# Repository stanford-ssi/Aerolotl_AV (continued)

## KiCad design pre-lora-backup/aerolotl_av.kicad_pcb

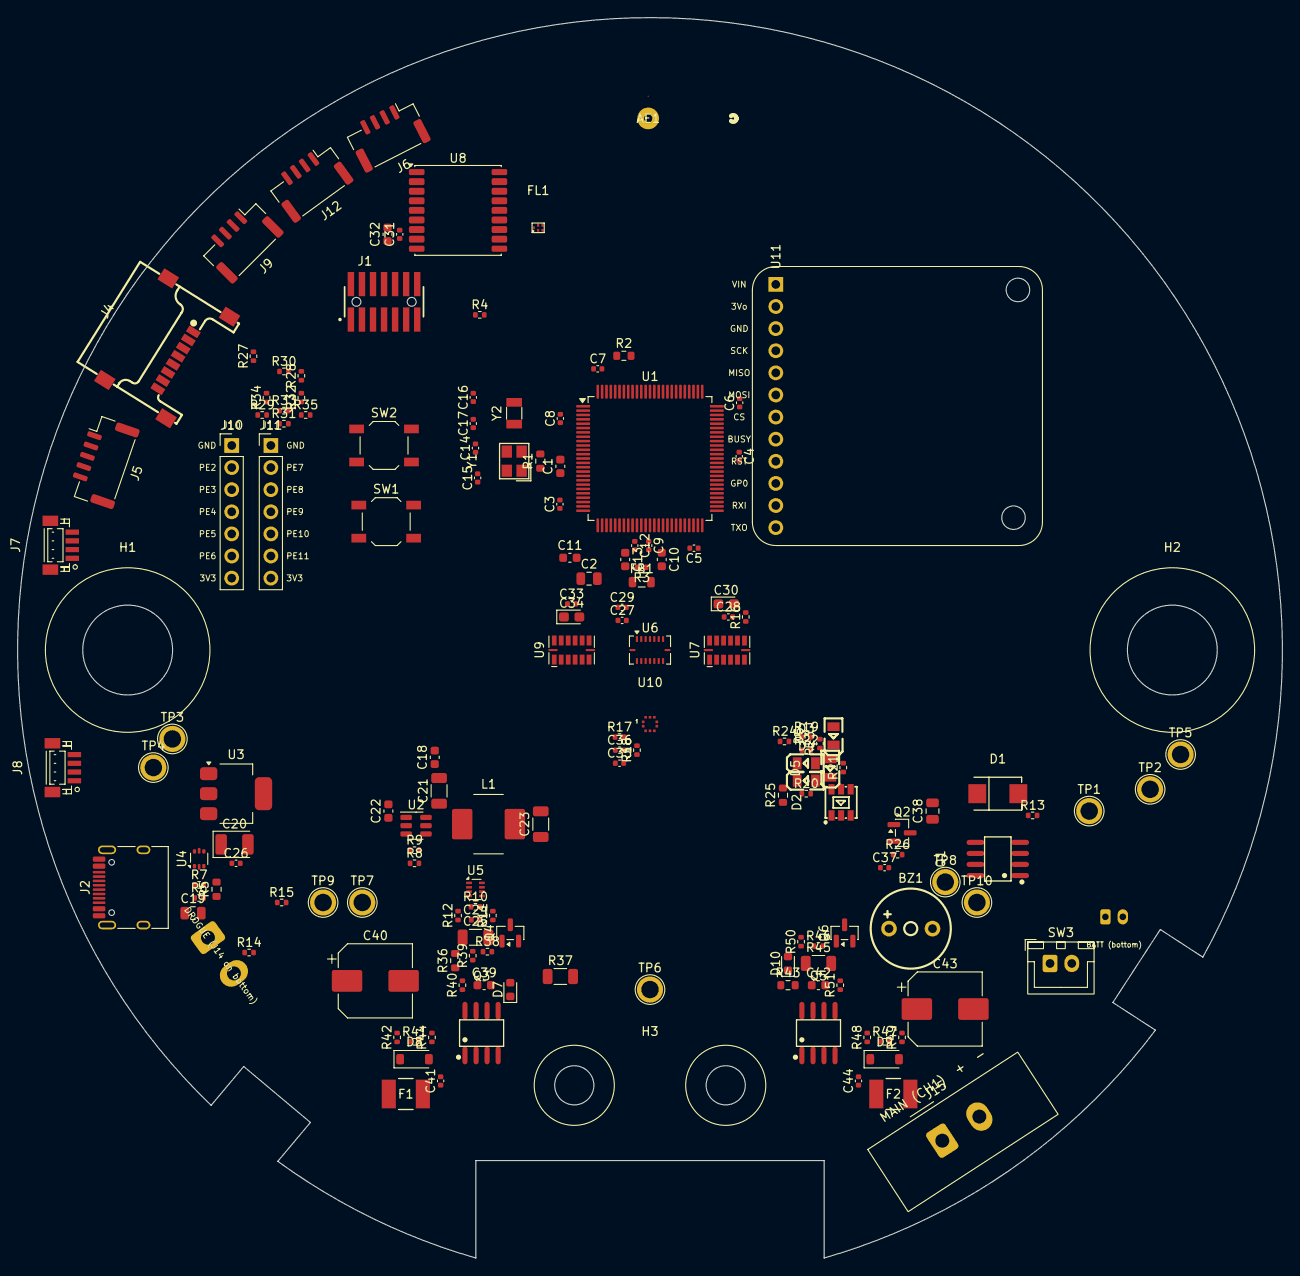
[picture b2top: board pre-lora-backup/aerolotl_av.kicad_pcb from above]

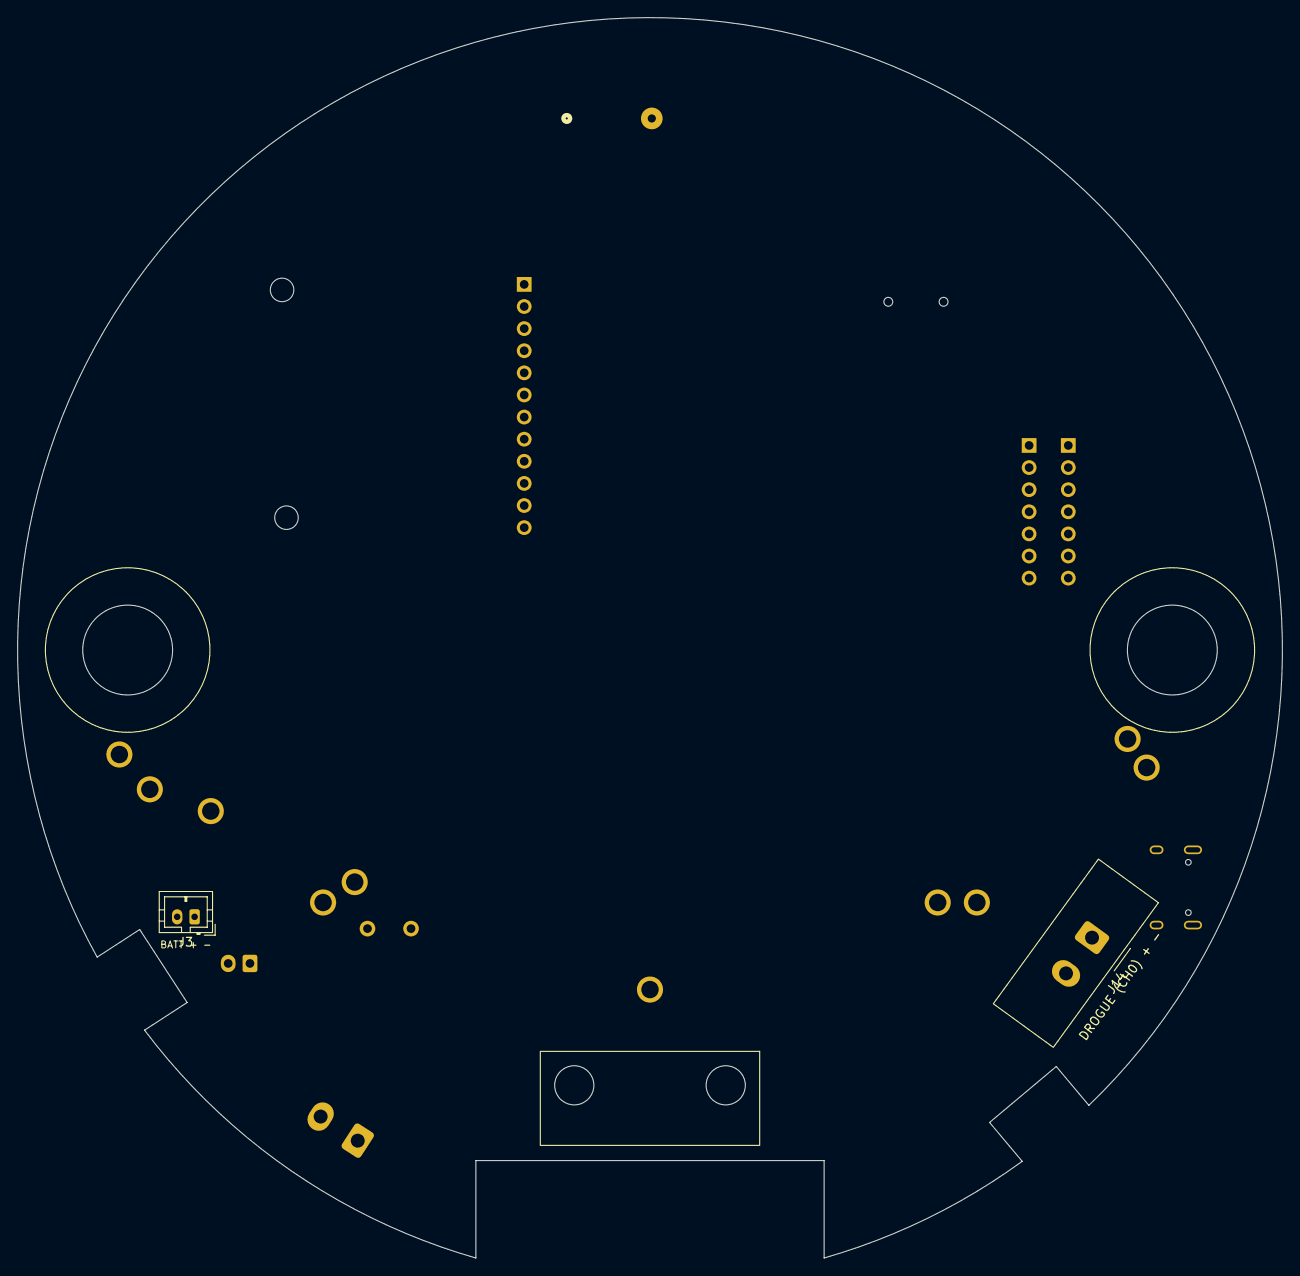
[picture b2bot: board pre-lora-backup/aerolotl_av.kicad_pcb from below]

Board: 4 copper layers, 145.3 x 142.5 mm, 161 parts (2 on the bottom side), 125 nets, no tracks yet.

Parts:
AE1: GP.1575.18.4.A.02; ANT_GP.1575.18.4.A.02_TAL
BZ1: HNB09A03; BUZ-TH_BD9.0-P5.00-D0.6-FD
C1, C18, C22: 100n; C_0603_1608Metric
C2: 4u7; C_0805_2012Metric
C3, C4, C5, C6, C7, C8, C12, C27, C28, C29, C31, C33, C35, C36, C37, C41, C44: 100n; C_0402_1005Metric
C9: 10n; C_0402_1005Metric
C10, C11, C13: 1u; C_0603_1608Metric
C14, C15: 15p; C_0402_1005Metric
C16, C17: 4.7p; C_0402_1005Metric
C19: 10u; C_0805_2012Metric
C20: 22u; CP_EIA-3528-21_Kemet-B
C21: 10u; C_1206_3216Metric
C23, C25: 100u; C_1206_3216Metric
C24, C26: 1u; C_0402_1005Metric
C30, C34: 1u; CP_EIA-2012-12_Kemet-R
C32: 10u; C_0603_1608Metric
C38: 22u; C_0805_2012Metric
C39, C42: 150n; C_0603_1608Metric
C40, C43: 330u; CP_Elec_8x10
D1: SMBJ15A; SMB_L4.6-W3.6-LS5.3-RD
D2: RS-3535MWAR-2JYJY-J; LED-SMD_RS-3535MWAR-2JYJY-J
D3: STM LED; LED0805-R-RD
D4: 3V3 LED; LED0805-R-RD
D5: USB LED; LED0805-R-RD
D6: ARM LED; LED0805-R-RD
D7, D10: LED red; LED_0603_1608Metric
D8, D9: 1N4148W; D_SOD-123
F1, F2: 1812L150/24MR; FUSE_1812L150&slash_24_LTF
FB1: 100; L_0805_2012Metric
FL1: B39162B4300F210; FILTER-SMD_5P-L1.4-W1.1_RSFPXXXXD
H1, H2: MountingHole; MountingHole_ThreadedRod_3-8in_D10.32mm
H3: TeleMetrum sled; TeleMetrum_Sled_Mount_2xM4
J1: FTSH-107-STDC14; STDC14_SAMTEC_FTSH-107-01-L-DV-K-A
J2: USB_C_Receptacle_USB2.0_16P; USB_C_Receptacle_HRO_TYPE-C-31-M-12
J3: Battery (ext.); JST_PH_B2B-PH-K_1x02_P2.00mm_Vertical
J4: TF-102-15_SD_read; TF-SMD_TF-102-15
J5: Conn_01x05_Pin; JST_GH_BM05B-GHS-TBT_1x05-1MP_P1.25mm_Vertical
J6: USART3; JST_GH_BM04B-GHS-TBT_1x04-1MP_P1.25mm_Vertical
J7, J8: StemmaQT
J9: Conn_01x04_Pin; JST_GH_BM04B-GHS-TBT_1x04-1MP_P1.25mm_Vertical
J10: GPIO_PE2-PE6; PinHeader_1x07_P2.54mm_Vertical
J11: GPIO_PE7-PE11; PinHeader_1x07_P2.54mm_Vertical
J12: LPUART1; JST_GH_BM04B-GHS-TBT_1x04-1MP_P1.25mm_Vertical
J14, J15: Screw_Terminal_01x02; TerminalBlock_Kangnex_WJ2EDGVM-5.08-02P_1x02_P5.08mm_Vertic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
L1: 5.6u; L_Cjiang_FXL0630_7.0x6.6mm
Q1: AO4407A; SOIC-8_L4.9-W3.9-P1.27-LS6.0-BL
Q2, Q4, Q6: AO3400A; SOT-23
Q3, Q5: FDS6673BZ_C467780; SOIC-8_L4.9-W3.9-P1.27-LS6.0-BL
R1, R2: 10k; R_0603_1608Metric
R3: 47; R_0402_1005Metric
R4, R38, R46: 100; R_0402_1005Metric
R5: 0R; R_0603_1608Metric
R6, R7: 5k1; R_0402_1005Metric
R8, R13: 100k; R_0402_1005Metric
R9: 22k1; R_0402_1005Metric
R10: 9k53; R_0402_1005Metric
R11, R14, R27, R28, R29, R30, R31, R41, R44, R47, R49: 10k; R_0402_1005Metric
R12: 4k99; R_0402_1005Metric
R15, R26: 3k3; R_0402_1005Metric
R16, R17, R18, R32, R33, R34, R35: 10; R_0402_1005Metric
R19, R20, R21, R40, R51: 330; R_0402_1005Metric
R22, R23: 470; R_0402_1005Metric
R24: 910; R_0402_1005Metric
R25, R36, R43: 3k3; R_0603_1608Metric
R37, R45: 1k; R_1206_3216Metric
R39, R50: 8k2; R_0402_1005Metric
R42, R48: 33k; R_0402_1005Metric
SW1: SW_SPST; SW_SPST_TL3342
SW2: SW_Push; SW_SPST_TL3342
SW3: SW_SPST; JST_XH_B2B-XH-A_1x02_P2.50mm_Vertical
TP1: +BATT; TestPoint_Plated_Hole_D2.0mm
TP2: +12V; TestPoint_Plated_Hole_D2.0mm
TP3: +3V3; TestPoint_Plated_Hole_D2.0mm
TP4: VOLT_SENSE; TestPoint_Plated_Hole_D2.0mm
TP5: GND; TestPoint_Plated_Hole_D2.0mm
TP6: +12V_ARM; TestPoint_Plated_Hole_D2.0mm
TP7: SENSE_I0; TestPoint_Plated_Hole_D2.0mm
TP8: SENSE_I1; TestPoint_Plated_Hole_D2.0mm
TP9: IGNITE_0; TestPoint_Plated_Hole_D2.0mm
TP10: IGNITE_1; TestPoint_Plated_Hole_D2.0mm
U1: STM32G474VETx; LQFP-100_14x14mm_P0.5mm
U2: LMR51430XFDDCR; TSOT-23-6
U3: AMS1117-3.3; SOT-223-3_TabPin2
U4: USBLC6-2P6; SOT-666
U5: TPS2116DRL; SOT-583-8
U6: BMI088; Bosch_LGA-16_4.5x3mm_P0.5mm_LayoutBorder7x1y_ClockwisePinNu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
U7: ADXL345BCCZ-RL7; ADI_LGA-14_3x5mm_P0.8mm
U8: MAX-M10S; ublox_MAX
U9: ADXL375BCCZ-RL7; ADI_LGA-14_3x5mm_P0.8mm
U10: BMP581; LGA-10_L2.0-W2.0-P0.50-TL_BMP581
U11: Airlift; Ada_Airlift
Y1: 25MHz; CRYSTAL-SMD_4P-L3.2-W2.5-BL
Y2: 32.768kHz; Crystal_SMD_3215-2Pin_3.2x1.5mm

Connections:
+3.3VA: C9.1, C10.1, FB1.1, R3.1, U1.37 (VDDA)
+3V3: BZ1.1 (+), C2.1, C3.1, C4.1, C5.1, C6.1, C7.1, C8.1, C11.1, C25.1, C27.1, C28.1, C29.1, C31.1, C32.1, C33.1, C34.1, C37.1, C38.1, D2.4 (A), D2.5 (A), D2.6 (A), D4.1 (+), D8.2 (A), D9.2 (A), FB1.2, J1.03, J4.4 (VDD), J5.5, J6.4, J7.2, J8.2, J9.4, J10.7, J11.7, J12.4, R1.1, R11.1, R16.1, R17.1, R18.1, R27.1, R28.1, R29.1, R30.1, R31.1, SW1.2 (B), TP3.1 (1_1), U1.6 (VBAT), U1.24 (VDD), U1.49 (VDD), U1.64 (VDD), U1.75 (VDD), U1.100 (VDD), U5.2 (VOUT), U5.7 (VOUT), U6.3 (VDD), U6.11 (VDDIO), U7.1 (VDD_I/O), U7.3 (RESERVED_3), U8.6 (V_BCKP), U8.7 (VCC_IO), U8.8 (VCC), U9.1 (VDDI/O), U9.3 (RESERVED), U9.6 (VS), U11.1 (VIN)
+3V3_BAT: C23.1, C24.1, L1.2, R8.1, R10.1, U5.3 (VIN1), U5.5 (MODE)
+5V: D5.1 (+), R5.1
+12V: C21.1, C22.1, D1.1, Q1.1 (S), Q1.2 (S), Q1.3 (S), R14.1, SW3.1 (A), TP2.1 (1_1), U2.3 (VIN), U2.5 (EN)
+12V_ARM: C39.1, C40.1, C42.1, C43.1, D6.1 (+), Q3.1 (S), Q3.2 (S), Q3.3 (S), Q5.1 (S), Q5.2 (S), Q5.3 (S), R36.2, R37.1, R43.2, R45.1, SW3.2 (B), TP6.1 (1_1)
+BATT: J3.1, Q1.5 (D), Q1.6 (D), Q1.7 (D), Q1.8 (D), TP1.1 (1_1)
/Debugger/GNDDetect: J1.11, R4.2
/Debugger/T_NRST: C1.1, J1.12, R1.2, SW2.2, U1.14 (PG10/NRST)
/Debugger/T_SWCLK: J1.06, U1.77 (PA14)
/Debugger/T_SWDIO: J1.04, U1.76 (PA13)
/Debugger/T_SWO: J1.08, U1.90 (PB3)
/Debugger/T_VCP_RX: J1.14, U1.70 (PA9)
/Debugger/T_VCP_TX: J1.13, U1.71 (PA10)
/External/GPIO.PE2: J10.2, U1.1 (PE2)
/External/GPIO.PE3: J10.3, U1.2 (PE3)
/External/GPIO.PE4: J10.4, U1.3 (PE4)
/External/GPIO.PE5: J10.5, U1.4 (PE5)
/External/GPIO.PE6: J10.6, U1.5 (PE6)
/External/GPIO.PE7: J11.2, U1.38 (PE7)
/External/GPIO.PE8: J11.3, U1.39 (PE8)
/External/GPIO.PE9: J11.4, U1.40 (PE9)
/External/GPIO.PE10: J11.5, U1.41 (PE10)
/External/GPIO.PE11: J11.6, U1.42 (PE11)
/External/I2C1.SCL: J7.4, U1.78 (PA15)
/External/I2C1.SDA: J7.3, U1.94 (PB7)
/External/I2C3.SCL: J8.4, U1.67 (PC8)
/External/I2C3.SDA: J8.3, U1.68 (PC9)
/External/I2C4.SCL: J9.2, U1.65 (PC6)
/External/I2C4.SDA: J9.3, U1.66 (PC7)
/External/LPUART1_TARGET_RX: J12.2, U1.47 (PB10)
/External/LPUART1_TARGET_TX: J12.3, U1.50 (PB11)
/External/SPI4.MISO: J5.3, U1.44 (PE13)
/External/SPI4.MOSI: J5.2, U1.45 (PE14)
/External/SPI4.SCK: J5.4, U1.43 (PE12)
/External/USART3_TARGET_RX: J6.2, U1.56 (PD9)
/External/USART3_TARGET_TX: J6.3, U1.55 (PD8)
/Igniter/IGN0: D7.2 (A), Q4.1 (G), R39.1, TP9.1 (1_1), U1.61 (PD14)
/Igniter/IGN0_CONT: J14.1, Q3.5 (D), Q3.6 (D), Q3.7 (D), Q3.8 (D), R41.2, R42.1
/Igniter/IGN0_DRV: Q4.3 (D), R38.2
/Igniter/IGN0_HS_GATE: C39.2, Q3.4 (G), R37.2, R38.1
/Igniter/IGN0_LED_K: D7.1 (K), R40.1
/Igniter/IGN0_RTN: F1.2, J14.2
/Igniter/IGN1: D10.2 (A), Q6.1 (G), R50.1, TP10.1 (1_1), U1.62 (PD15)
/Igniter/IGN1_CONT: J15.1, Q5.5 (D), Q5.6 (D), Q5.7 (D), Q5.8 (D), R47.2, R48.1
/Igniter/IGN1_DRV: Q6.3 (D), R46.2
/Igniter/IGN1_HS_GATE: C42.2, Q5.4 (G), R45.2, R46.1
/Igniter/IGN1_LED_K: D10.1 (K), R51.1
/Igniter/IGN1_RTN: F2.2, J15.2
/Igniter/SENSE_I0: C41.1, R42.2, R44.1, TP7.1 (1_1), U1.20 (PA0)
/Igniter/SENSE_I1: C44.1, R48.2, R49.1, TP8.1 (1_1), U1.21 (PA1)
/Indicators/BUZZER: Q2.1 (G), R26.1, U1.69 (PA8)
/Indicators/BUZZER_DRV: BZ1.2 (-), Q2.3 (D)
/Indicators/LED: D3.1 (+), U1.60 (PD13)
/Indicators/LED.B: R21.2, U1.59 (PD12)
/Indicators/LED.G: R20.2, U1.31 (PC5)
/Indicators/LED.R: R19.2, U1.30 (PC4)
/Indicators/LED_3V3_K: D4.2 (-), R23.1
/Indicators/LED_ARM_K: D6.2 (-), R25.1
/Indicators/LED_STM_K: D3.2 (-), R22.1
/Indicators/LED_USB_K: D5.2 (-), R24.1
/Indicators/RGB_B_K: D2.1 (K), R21.1
/Indicators/RGB_G_K: D2.2 (K), R20.1
/Indicators/RGB_R_K: D2.3 (K), R19.1
/MCU/BOOT0: R2.1, SW1.1 (A), U1.95 (PB8/BOOT0)
/MCU/GPS_RST: U1.91 (PB4), U8.9 (~RESET)
/MCU/HS_OSC_A: C14.1, U1.12 (PF0), Y1.1 (OSC1)
/MCU/HS_OSC_B: C15.1, U1.13 (PF1), Y1.3 (OSC2)
/MCU/LS_OSC_A: C17.1, U1.8 (PC14), Y2.2
/MCU/LS_OSC_B: C16.1, U1.9 (PC15), Y2.1
/MCU/PWR_STS: R11.2, U1.16 (PC1), U5.8 (ST)
/MCU/SDSPI.CS: R33.1, U1.82 (PD0)
/MCU/SDSPI.MISO: R35.1, U1.80 (PC11)
/MCU/SDSPI.MOSI: R32.1, U1.81 (PC12)
/MCU/SDSPI.SCK: R34.1, U1.79 (PC10)
/MCU/SPI1.CS_345: U1.88 (PD6), U7.7 (~CS)
/MCU/SPI1.CS_375: U1.89 (PD7), U9.7 (~CS)
/MCU/SPI1.CS_BMP: U1.87 (PD5), U10.6 (CSB)
/MCU/SPI1.CS_IMU_ACC: U1.85 (PD3), U6.14 (~CSB1)
/MCU/SPI1.CS_IMU_GYRO: U1.86 (PD4), U6.5 (~CSB2)
/MCU/SPI1.INT_345: U1.32 (PB0), U7.8 (INT1)
/MCU/SPI1.INT_375: U1.96 (PB9), U9.8 (INT1)
/MCU/SPI1.INT_BMP: U1.33 (PB1), U10.7 (INT)
/MCU/SPI1.INT_IMU_ACC: U1.46 (PE15), U6.16 (INT1)
/MCU/SPI1.INT_IMU_GYRO: U1.34 (PB2), U6.12 (INT3)
/MCU/SPI1.MISO: U1.28 (PA6), U6.10 (SDO2), U6.15 (SDO1), U7.12 (SDO/ALT_ADDRESS), U9.12 (SDO/ALTADDRESS), U10.5 (SDO)
/MCU/SPI1.MOSI: U1.29 (PA7), U6.9 (SDI/SDA), U7.13 (SDA/SDI/SDIO), U9.13 (SDA/SDI/SDIO), U10.4 (SDI)
/MCU/SPI1.SCK: U1.27 (PA5), U6.8 (SCK/SCL), U7.14 (SCL/SCLK), U9.14 (SCL/SCLK), U10.2 (SCK)
/MCU/SPI2.BUSY: U1.57 (PD10), U11.8 (BUSY)
/MCU/SPI2.CS: U1.51 (PB12), U11.7 (CS)
/MCU/SPI2.MISO: U1.53 (PB14), U11.5 (MISO)
/MCU/SPI2.MOSI: U1.54 (PB15), U11.6 (MOSI)
/MCU/SPI2.RST: U1.58 (PD11), U11.9 (~RST)
/MCU/SPI2.SCK: U1.52 (PB13), U11.4 (SCK)
/MCU/USB_D+: U1.73 (PA12), U4.4 (I/O2)
/MCU/USB_D-: U1.72 (PA11), U4.6 (I/O1)
/MCU/VREFP: C12.1, C13.1, R3.2, U1.36 (VREF+)
/Power/BUCK_CB: C18.1, U2.6 (CB)
/Power/BUCK_FB: R8.2, R9.1, U2.4 (FB)
/Power/BUCK_SW: C18.2, L1.1, U2.2 (SW)
/Power/PMUX_PR1: R10.2, R12.1, U5.4 (PR1)
/Power/P_VBUS: C19.1, J2.A4 (VBUS), J2.A9 (VBUS), J2.B4 (VBUS), J2.B9 (VBUS), R5.2, U3.3 (VI), U4.5 (VBUS)
/Power/RPP_GATE: Q1.4 (G), R13.1
/Power/USB_3V3: C20.1, C26.1, U3.2 (VO), U5.6 (VIN2)
/Power/USB_CC1: J2.A5 (CC1), R6.1
/Power/USB_CC2: J2.B5 (CC2), R7.1
/Power/USB_DM: J2.A7 (D-), J2.B7 (D-), U4.1 (I/O1)
/Power/USB_DP: J2.A6 (D+), J2.B6 (D+), U4.3 (I/O2)
/Power/VOLT_SENSE: R14.2, R15.1, TP4.1 (1_1), U1.15 (PC0)
/SD/CARD_CS: J4.2 (CD/DAT3), R30.2, R33.2
/SD/CARD_DAT1: J4.8 (DAT1), R27.2
/SD/CARD_DAT2: J4.1 (DAT2), R31.2
/SD/CARD_MISO: J4.7 (DAT0), R28.2, R35.2
/SD/CARD_MOSI: J4.3 (CMD), R29.2, R32.2
/SD/CARD_SCK: J4.5 (CLK), R34.2
/Sensors/ADXL345_VS: C30.1, R16.2, U7.6 (VS)
/Sensors/BMP581_VDD: C35.1, R18.2, U10.10 (VDD)
/Sensors/BMP581_VDDIO: C36.1, R17.2, U10.1 (VDDIO)
/Sensors/GPS_RF_ANT: AE1.1 (1_1), FL1.1 (IN)
/Sensors/GPS_RF_IN: FL1.4 (OUT), U8.11 (RF_IN)
/Sensors/M10S.RX: U1.22 (PA2), U8.3 (RXD)
/Sensors/M10S.TX: U1.25 (PA3), U8.2 (TXD)
GND: C1.2, C2.2, C3.2, C4.2, C5.2, C6.2, C7.2, C8.2, C9.2, C10.2, C11.2, C12.2, C13.2, C14.2, C15.2, C16.2, C17.2, C19.2, C20.2, C21.2, C22.2, C23.2, C24.2, C25.2, C26.2, C27.2, C28.2, C29.2, C30.2, C31.2, C32.2, C33.2, C34.2, C35.2, C36.2, C37.2, C38.2, C40.2, C41.2, C43.2, C44.2, D1.2, F1.1, F2.1, FL1.2 (GND), FL1.3 (GND), FL1.5 (GND), J1.05, J1.07, J2.A1 (GND), J2.A12 (GND), J2.B1 (GND), J2.B12 (GND), J2.SH (SHIELD), J3.2, J4.6 (VSS), J4.9 (SHELL), J4.10 (SHELL), J4.11 (SHELL), J4.12 (SHELL), J5.1, J6.1, J7.0, J7.1, J8.0, J8.1, J9.1, J10.1, J11.1, J12.1, Q2.2 (S), Q4.2 (S), Q6.2 (S), R2.2, R4.1, R6.2, R7.2, R9.2, R12.2, R13.2, R15.2, R22.2, R23.2, R24.2, R25.2, R26.2, R36.1, R39.2, R40.2, R43.1, R44.2, R49.2, R50.2, R51.2, SW2.1, TP5.1 (1_1), U1.23 (VSS), U1.35 (VSSA), U1.48 (VSS), U1.63 (VSS), U1.74 (VSS), U1.99 (VSS), U2.1 (GND), U3.1 (GND), U4.2 (GND), U5.1 (GND), U6.2 (GNDA), U6.4 (GNDA), U6.6 (GNDIO), U6.7 (PS), U7.2 (GND), U7.4 (GND), U7.5 (GND), U7.11 (RESERVED_11), U8.1 (GND), U8.10 (GND), U8.12 (GND), U9.2 (GND), U9.4 (GND), U9.5 (GND), U9.11 (RESERVED), U10.3 (VSS), U10.8 (VSS), U10.9 (VSS), U11.3 (GND), Y1.2 (GND), Y1.4 (GND)
unnamed: D8.1 (K), R41.1
unnamed: D9.1 (K), R47.1

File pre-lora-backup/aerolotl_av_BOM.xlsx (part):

Designators | Qty | Value | Footprint | LCSC Part | MPN | Manufacturer | Voltage | Dielectric | Tolerance | ESR / DCR | Power | JLC library | JLC stock (2026-10-02) | Assembly | Side | Sheet | Notes / datasheet check
AE1 | 1 | GP.1575.18.4.A.02 | ANT_GP.1575.18.4.A.02_TAL | C7281913 | GP.1575.18.4.A.02 | Taoglas |  |  |  |  |  | Extended | 0 | Hand-place (no LCSC stock) | Top | sensors | Taoglas patch has an LCSC number but 0 stock. Order from Digikey/Mouser and han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
BZ1 | 1 | HNB09A03 | BUZ-TH_BD9.0-P5.00-D0.6-FD | C96102 | HNB09A03 | Huaneng |  |  |  |  |  | Extended | 44983 | JLC THT | Top | indicators | Active buzzer (internal oscillator): drive it on/off. PWM is only useful for be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
C1, C18, C22 | 3 | 100n | C_0603_1608Metric | C14663 | CC0603KRX7R9BB104 | YAGEO | 50V | X7R | 10% |  |  | Basic | 58141193 | JLC SMT | Top | mcu | LMR51430: 0.1uF HF bypass at VIN, 50V; LMR51430: CBOOT 0.1uF X7R >= 16V
C2 | 1 | 4u7 | C_0805_2012Metric | C98195 | CL21B475KAFNNNE | Samsung Electro-Mechanics | 25V | X7R | 10% |  |  | Extended | 311410 | JLC SMT | Top | mcu | STM32G474 DS12288 Fig.16: VDD n x 100nF + 1 x 4.7uF
C3, C4, C5, C6, C7, C8, C12, C27, C28, C29, C31, C33, C35, C36, C37, C41, C44 | 17 | 100n | C_0402_1005Metric | C1525 | CL05B104KO5NNNC | Samsung Electro-Mechanics | 16V | X7R | 10% |  |  | Basic | 21581667 | JLC SMT | Top | mcu | ADXL345 DS: 0.1uF ceramic at VDD I/O; ADXL375 DS: 0.1uF ceramic at VDD I/O; STM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
C9 | 1 | 10n | C_0402_1005Metric | C15195 | CL05B103KB5NNNC | Samsung Electro-Mechanics | 50V | X7R | 10% |  |  | Basic | 4033054 | JLC SMT | Top | mcu | STM32G474 DS12288 Fig.16: VDDA = 10nF + 1uF (was 100nF)
C10, C11, C13 | 3 | 1u | C_0603_1608Metric | C29936 | CL10B105KA8NNNC | Samsung Electro-Mechanics | 25V | X7R | 10% |  |  | Extended | 266599 | JLC SMT | Top | mcu | STM32G474 DS12288 Fig.16: VDDA 1uF; STM32G474 DS12288 Fig.16: VREF+ 100nF + 1uF
C14, C15 | 2 | 15p | C_0402_1005Metric | C1548 | 0402CG150J500NT | FH (Guangdong Fenghua) | 50V | C0G | 5% |  |  | Basic | 1431860 | JLC SMT | Top | mcu | HSE load cap, 12pF crystal: 2 x (12pF - ~4.5pF stray) = ~15pF
C16, C17 | 2 | 4.7p | C_0402_1005Metric | C1569 | 0402CG4R7C500NT | FH (Guangdong Fenghua) | 50V | C0G | 0.25pF |  |  | Extended (preferred) | 597482 | JLC SMT | Top | mcu | LSE load cap for 6pF crystal: CL = C/2 + Cs (Cs ~3.5-4pF)
C19 | 1 | 10u | C_0805_2012Metric | C15850 | CL21A106KAYNNNE | Samsung Electro-Mechanics | 25V | X5R | 10% |  |  | Basic | 4951626 | JLC SMT | Top | power | USB 2.0 allows at most 10uF on VBUS at attach (was 22uF)
C20 | 1 | 22u | CP_EIA-3528-21_Kemet-B | C8020 | TAJB226K016RNJ | Kyocera AVX | 16V | Tantalum (MnO2) | 10% | 2.3R @100kHz |  | Extended | 81310 | JLC SMT | Top | power | AMS1117 datasheet: 22uF solid tantalum on output for stability, needs its ESR (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
C21 | 1 | 10u | C_1206_3216Metric | C89632 | CL31B106KBHNNNE | Samsung Electro-Mechanics | 50V | X7R | 10% |  |  | Extended | 109372 | JLC SMT | Top | power | LMR51430 DS 9.2.2.6: CIN >= 4.7uF X5R/X7R, rated about 2x VIN max (12.6V) -> 50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
C23, C25 | 2 | 100u | C_1206_3216Metric | C15008 | CL31A107MQHNNNE | Samsung Electro-Mechanics | 6.3V | X5R | 20% |  |  | Basic | 1940643 | JLC SMT | Top | power | LMR51430 Table 9-1 (500kHz, 3.3V) asks for 2x22uF/25V. 100uF/6.3V X5R 1206 dera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
C24, C26 | 2 | 1u | C_0402_1005Metric | C52923 | CL05A105KA5NQNC | Samsung Electro-Mechanics | 25V | X5R | 10% |  |  | Basic | 5613299 | JLC SMT | Top | power
C30, C34 | 2 | 1u | CP_EIA-2012-12_Kemet-R | C444768 | TAJR105K010RNJ | Kyocera AVX | 10V | Tantalum (MnO2) | 10% | 25R @100kHz |  | Extended | 2570 | JLC SMT | Top | sensors | ADXL345 DS p.28: 1uF tantalum at VS; ADXL375 DS: 1uF tantalum at VS
C32 | 1 | 10u | C_0603_1608Metric | C19702 | CL10A106KP8NNNC | Samsung Electro-Mechanics | 10V | X5R | 10% |  |  | Basic | 10315650 | JLC SMT | Top | sensors
C38 | 1 | 22u | C_0805_2012Metric | C45783 | CL21A226MAQNNNE | Samsung Electro-Mechanics | 25V | X5R | 20% |  |  | Basic | 3990887 | JLC SMT | Top | indicators
C39, C42 | 2 | 150n | C_0603_1608Metric | C513735 | CC0603KRX7R9BB154 | YAGEO | 50V | X7R | 10% |  |  | Extended | 607110 | JLC SMT | Top | igniter | PMOS gate slow-turn-on cap across +12V_ARM: 50V
C40, C43 | 2 | 330u | CP_Elec_8x10 | C970701 | RVT1E331M0810 | DMBJ | 25V | Aluminum electrolytic | 20% | not specified (standard 105C SMD Al-El) |  | Extended | 1527 | JLC SMT | Top | igniter | Igniter reservoir on +12V_ARM (3S, 12.6V max): 25V rating
D1 | 1 | SMBJ15A | SMB_L4.6-W3.6-LS5.3-RD | C83846 | SMBJ15A | Littelfuse |  |  |  |  |  | Extended | 11134 | JLC SMT | Top | power
D2 | 1 | RS-3535MWAR-2JYJY-J | LED-SMD_RS-3535MWAR-2JYJY-J | C110402 | RS-3535MWAR | NATIONSTAR |  |  |  |  |  | Extended | 460049 | JLC SMT | Top | indicators | Check: G/B Vf ~2.8-3.2V on a 3.3V anode leaves <1mA through 330R (dim)
D3 | 1 | STM LED | LED0805-R-RD | C2296 | KT-0805Y | Hubei KENTO |  |  |  |  |  | Basic | 389526 | JLC SMT | Top | indicators
D4 | 1 | 3V3 LED | LED0805-R-RD | C2296 | KT-0805Y | Hubei KENTO |  |  |  |  |  | Basic | 389526 | JLC SMT | Top | indicators
D5 | 1 | USB LED | LED0805-R-RD | C2296 | KT-0805Y | Hubei KENTO |  |  |  |  |  | Basic | 389526 | JLC SMT | Top | indicators
D6 | 1 | ARM LED | LED0805-R-RD | C2296 | KT-0805Y | Hubei KENTO |  |  |  |  |  | Basic | 389526 | JLC SMT | Top | indicators
D7, D10 | 2 | LED red | LED_0603_1608Metric | C2286 | KT-0603R | Hubei KENTO |  |  |  |  |  | Basic | 4815898 | JLC SMT | Top | igniter
D8, D9 | 2 | 1N4148W | D_SOD-123 | C81598 | 1N4148W | ST(Semtech) |  |  |  |  |  | Basic | 5168664 | JLC SMT | Top | igniter
F1, F2 | 2 | 1812L150/24MR | FUSE_1812L150&slash_24_LTF | C142805 | 1812L150/24MR | Littelfuse |  |  |  |  |  | Extended | 14071 | JLC SMT | Top | igniter
FB1 | 1 | 100 | L_0805_2012Metric | C1015 | GZ2012D101TF | Sunlord |  |  |  |  |  | Basic | 2341388 | JLC SMT | Top | mcu
FL1 | 1 | B39162B4300F210 | FILTER-SMD_5P-L1.4-W1.1_RSFPXXXXD | C2650962 | B39162B4300F210 | Qualcomm (RF360) |  |  |  |  |  | Extended | 4559 | JLC SMT | Top | sensors
J1 | 1 | FTSH-107-STDC14 | STDC14_SAMTEC_FTSH-107-01-L-DV-K-A | C5563894 | FTSH-107-01-L-DV-K-A | Samtec |  |  |  |  |  | Extended | 540 | JLC SMT | Top | swd
J2 | 1 | USB_C_Receptacle_USB2.0_16P | USB_C_Receptacle_HRO_TYPE-C-31-M-12 | C165948 | TYPE-C-31-M-12 | Korean Hroparts |  |  |  |  |  | Extended | 426143 | JLC THT | Top | power
J3 | 1 | Battery (ext.) | JST_PH_B2B-PH-K_1x02_P2.00mm_Vertical | C131337 | B2B-PH-K-S(LF)(SN) | JST |  |  |  |  |  | Extended | 63611 | Hand-solder (bottom side) | Bottom | power | External battery input (+BATT / GND) on the bottom side, hand-solder. JST PH is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
J4 | 1 | TF-102-15_SD_read | TF-SMD_TF-102-15 | C266609 | TF-102-15 | XUNPU |  |  |  |  |  | Extended | 19063 | JLC SMT | Top | sd
J5 | 1 | Conn_01x05_Pin | JST_GH_BM05B-GHS-TBT_1x05-1MP_P1.25mm_Vertical | C189891 | BM05B-GHS-TBT(LF)(SN)(N) | JST |  |  |  |  |  | Extended | 9667 | JLC SMT | Top | external
J6 | 1 | USART3 | JST_GH_BM04B-GHS-TBT_1x04-1MP_P1.25mm_Vertical | C161692 | BM04B-GHS-TBT(LF)(SN) | JST |  |  |  |  |  | Extended | 14065 | JLC SMT | Top | external
J7, J8 | 2 | StemmaQT | StemmaQT | C160390 | BM04B-SRSS-TB(LF)(SN) | JST |  |  |  |  |  | Extended | 52346 | JLC SMT | Top | external
J9 | 1 | Conn_01x04_Pin | JST_GH_BM04B-GHS-TBT_1x04-1MP_P1.25mm_Vertical | C161692 | BM04B-GHS-TBT(LF)(SN) | JST |  |  |  |  |  | Extended | 14065 | JLC SMT | Top | external
J10 | 1 | GPIO_PE2-PE6 | PinHeader_1x07_P2.54mm_Vertical | C492406 | PZ254V-11-07P | XFCN |  |  |  |  |  | Extended | 50677 | JLC THT | Top | external
J11 | 1 | GPIO_PE7-PE11 | PinHeader_1x07_P2.54mm_Vertical | C492406 | PZ254V-11-07P | XFCN |  |  |  |  |  | Extended | 50677 | JLC THT | Top | external
J12 | 1 | LPUART1 | JST_GH_BM04B-GHS-TBT_1x04-1MP_P1.25mm_Vertical | C161692 | BM04B-GHS-TBT(LF)(SN) | JST |  |  |  |  |  | Extended | 14065 | JLC SMT | Top | external
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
